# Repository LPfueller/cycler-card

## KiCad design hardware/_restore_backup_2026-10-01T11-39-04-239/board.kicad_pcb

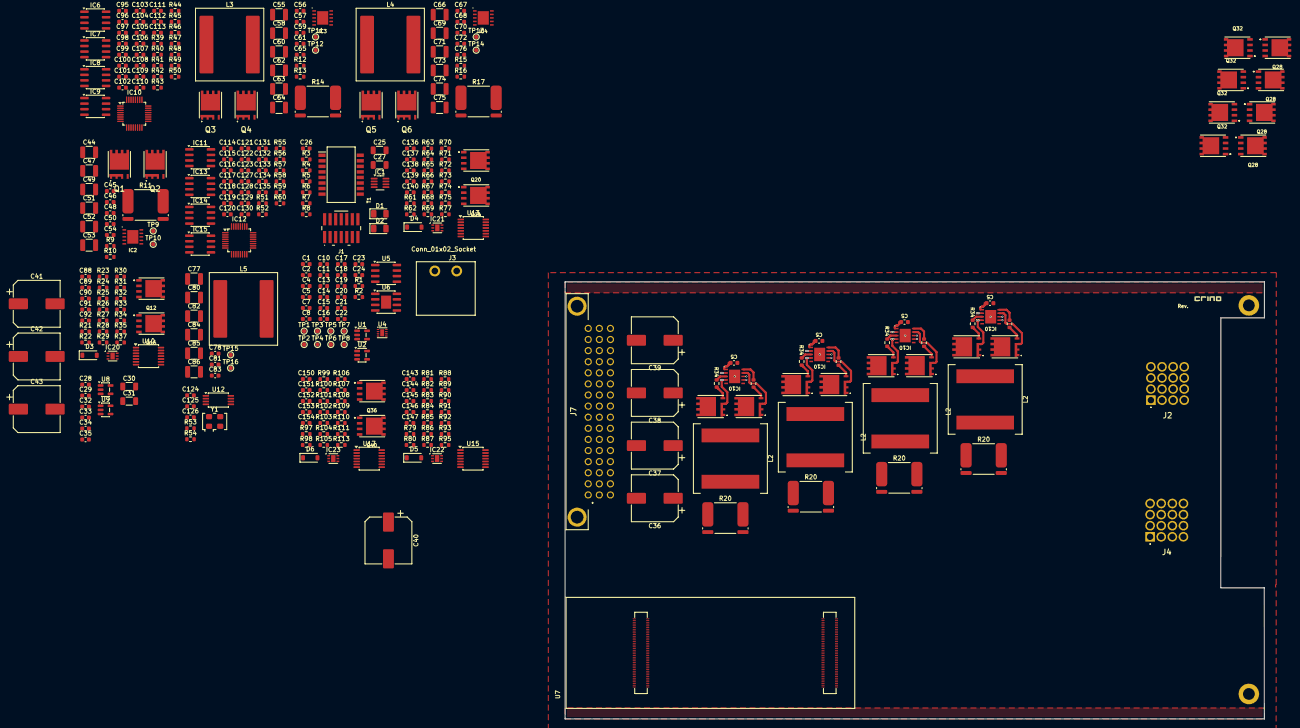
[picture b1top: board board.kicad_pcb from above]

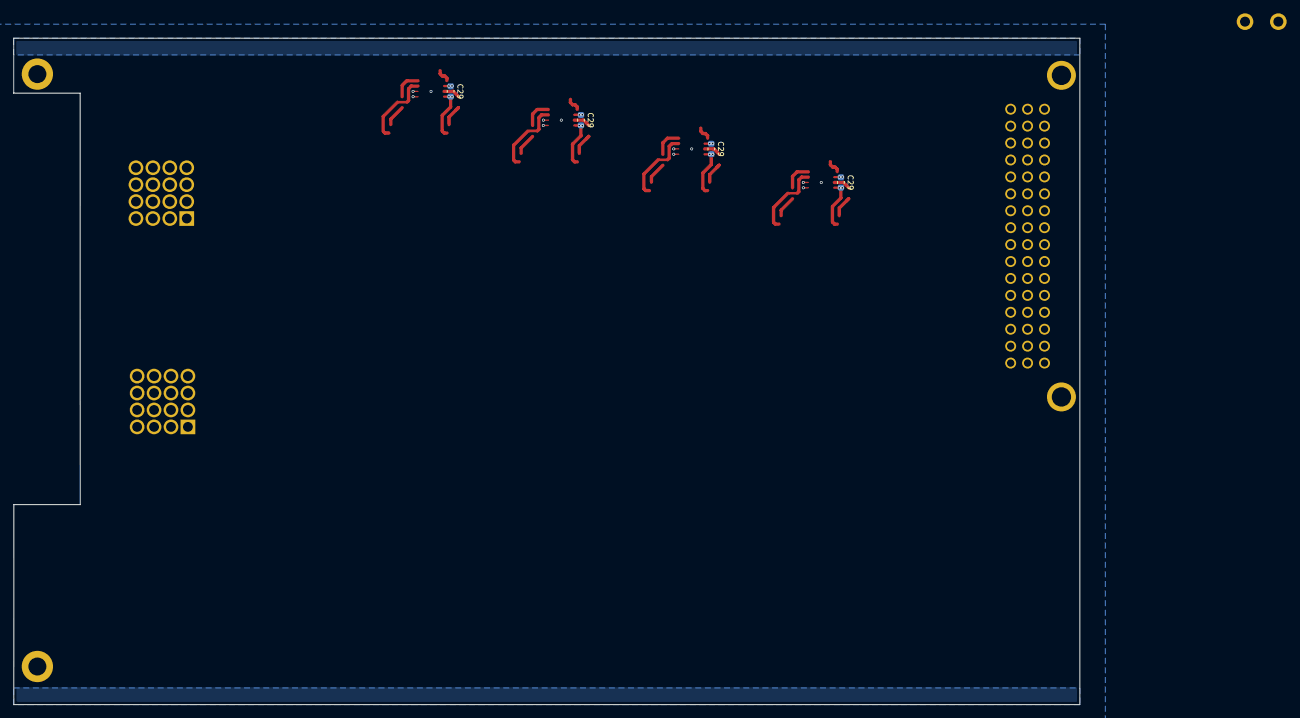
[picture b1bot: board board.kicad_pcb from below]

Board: 4 copper layers, 160.0 x 100.0 mm, 367 parts (4 on the bottom side), 222 nets.

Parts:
C1, C2, C10, C11, C15, C16, C20, C21, C23, C34, C35: 2.2u; C_0603_1608Metric
C4, C5#2, C7, C8, C17, C22, C24, C26, C29#2, C29#3, C29#4, C29#5, C32, C33, C45, C48, C50, C54, C56, C59, C61, C65, C67, C70, C72, C76, C78, C81, C83, C88, C89, C92, C95, C96, C97, C98, C99, C100, C101, C102, C108, C109, C113, C114, C115, C118, C119, C123, C124, C126, C127, C128, C130, C131, C133, C134, C136, C137, C140, C143, C144, C147, C150, C151, C154: 100n; C_0603_1608Metric
C5, C5#3, C5#4, C5#5, C14, C28, C29, C46, C57, C68, C90, C91, C107, C110, C111, C112, C117, C120, C121, C122, C125, C138, C139, C145, C146, C152, C153: 1u; C_0603_1608Metric
C13, C18: 4.7u; C_0603_1608Metric
C19: 1n; C_0603_1608Metric
C25, C27: 1n; C_1206_3216Metric
C30, C31: C; C_1206_3216Metric
C36, C37, C38, C39, C40, C41, C42, C43: 270u; CP_Elec_10x12.5
C44, C47, C49, C51, C52, C53, C55, C58, C60, C62, C63, C64, C66, C69, C71, C73, C74, C75, C77, C80, C82, C84, C85, C86: 10u; C_1210_3225Metric
C103, C104, C105, C106, C116, C129, C132, C135: 330n; C_0603_1608Metric
D1: LED_SYNC; LED_1206_3216Metric
D2: LED_ERR; LED_1206_3216Metric
D3, D4, D5, D6: 1N5817; D_SOD-123
H7, H8: MountingHole; MountingHole_2.7mm_M2.5_DIN965_Pad
H9: CrinoLogo; crino_logo
IC1: TCAN1044VDDFR; SOT-23-8_Handsoldering
IC2, IC3, IC4, IC10#2, IC10#3, IC10#4, IC10#5: UCC27212DPRR; SON80P400X400X80-11N-D
IC6, IC7, IC8, IC9, IC11, IC13, IC14, IC15: INA821ID; SOIC-8_3.9x4.9mm_P1.27mm
IC10, IC12: ADS131A04IPBS; LQFP-32_5x5mm_P0.5mm
IC20, IC21, IC22, IC23: NCV68261; DFN-6-1EP_2x2mm_P0.65mm_EP1x1.6mm
J1: Conn_ST_STDC14; FTSH-107-01-L-DV-K-TR
J2: +FORCE; 7461147
J3: Conn_01x02_Socket; Wago_231-432_001-000
J4: -FORCE; 7461147
J7: 09231482921
L2, L2#2, L2#3, L2#4, L3, L4, L5: 4.7u; L_Coilcraft_XAL1510-472
Q1, Q1#2, Q1#3, Q1#4, Q1#5, Q2, Q3, Q4, Q5, Q6, Q16, Q16#2, Q16#3, Q16#4: ISC012N04LM6; ISC012N04LM6ATMA1
Q12, Q16#5, Q20, Q24, Q28, Q28#2, Q28#3, Q28#4, Q32, Q32#2, Q32#3, Q32#4, Q36, Q40: SIRA60DP; SI7852ADPT1GE3
R1: 150k; R_0603_1608Metric
R2, R23, R63, R81, R99: 49.9k; R_0603_1608Metric
R3, R4, R5, R6: 75; R_0603_1608Metric
R7: 1.2k; R_0603_1608Metric
R8: 560; R_0603_1608Metric
R9, R10, R12, R13, R15, R15#2, R15#3, R15#4, R15#5, R16, R32, R34, R34#2, R34#3, R34#4, R34#5, R35, R72, R74, R75, R90, R92, R93, R108, R110, R111: 0; R_0603_1608Metric
R11, R14, R17, R20, R20#2, R20#3, R20#4: 1m; R_Shunt_Isabellenhuette_BVR4026
R21, R22, R61, R62, R79, R80, R97, R98: 100k; R_0603_1608Metric
R24, R64, R82, R100: 24.9k; R_0603_1608Metric
R25, R26, R65, R66, R83, R84, R101, R102: 4.99k; R_0603_1608Metric
R27, R28, R29, R30, R31, R33, R53, R54, R67, R68, R69, R70, R71, R73, R85, R86, R87, R88, R89, R91, R103, R104, R105, R106, R107, R109: 10k; R_0603_1608Metric
R37, R77, R95, R113: 10; R_0603_1608Metric
R39, R40, R41, R42: R_0603_1608Metric
R43, R44, R45, R46, R47, R48, R49, R50, R51, R52, R55, R56, R57, R58, R59, R60: 1k; R_0603_1608Metric
T1: H1102NLT; SOIC127P940X622-16N
TP1, TP2, TP3, TP4, TP5, TP6, TP7, TP8, TP9, TP10, TP11, TP12, TP13, TP14, TP15, TP16: Testpoint; TestPoint_Pad_D1.0mm
U1, U9: LP2985-5.0; SOT-23-5
U2: LP2985-10.0; SOT-23-5
U4: LM27761; Texas_DSG0008A_WSON-8-1EP_2x2mm_P0.5mm_EP0.9x1.6mm
U5: MAX6225; SOIC-8_3.9x4.9mm_P1.27mm
U6: ADP7142ARDZ-5.0; SOIC-8-1EP_3.9x4.9mm_P1.27mm_EP2.29x3mm
U7: crino-board
U8: LP2985-3.3; SOT-23-5
U10, U13, U15, U17: LM339; TSSOP-14_4.4x5mm_P0.65mm
U12: CDCV304; TSSOP-8_4.4x3mm_P0.65mm
Y1: ASFLMB-16.384MHZ-LR-T; Oscillator_SMD_EuroQuartz_XO53-4Pin_5.0x3.2mm

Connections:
/+2.5VREF: C20.2, C22.2, IC6.6 (REF), IC7.6 (REF), IC8.6 (REF), IC9.6 (REF), IC10.14 (REFEXT), IC12.14 (REFEXT), R44.1, R46.1, R48.1, R50.1, R52.1, R56.1, R58.1, R60.1, TP3.1 (1_1), U5.6 (OUT)
/+3.3V: C34.2, C107.1, C108.1, C109.1, C117.1, C118.1, C119.1, C124.1, C125.1, C126.1, IC10.15 (IOVDD_1), IC10.16 (RESV), IC10.29 (IOVDD_2), IC12.15 (IOVDD_1), IC12.16 (RESV), IC12.29 (IOVDD_2), J1.3 (VCC), R53.2, R54.2, U7.J2_23 (+3V3), U7.J2_34 (+3V3_1), U7.J2_43 (+3V3_2), U7.J2_69 (+3V3_3), U8.5 (VOUT), U12.6 (V_{DD}), Y1.4 (VDD)
/+5V: C26.1, C35.2, IC1.3 (VCC), IC1.5 (VIO), R7.1, R8.1, R31.2, R71.2, R89.2, R107.2, U9.5 (VOUT)
/+5VA: C23.2, C24.2, C111.1, C113.1, C121.1, C123.1, IC10.9 (AVDD), IC12.9 (AVDD), TP6.1 (1_1), U6.1 (VOUT), U6.2 (VOUT), U6.3 (SENSE/ADJ)
/+10VA: C1.2, C4.2, C11.2, C15.2, C16.2, C17.2, C88.1, C91.1, C92.1, C95.1, C96.1, C97.1, C98.1, C114.1, C127.1, C130.1, C133.1, C136.1, C139.1, C140.1, C143.1, C146.1, C147.1, C150.1, C153.1, C154.1, IC6.8 (+VS), IC7.8 (+VS), IC8.8 (+VS), IC9.8 (+VS), IC11.8 (+VS), IC13.8 (+VS), IC14.8 (+VS), IC15.8 (+VS), IC20.6 (IN), IC21.6 (IN), IC22.6 (IN), IC23.6 (IN), R24.1, R64.1, R82.1, R100.1, TP1.1 (1_1), U1.1 (VIN), U1.3 (ON/~OFF), U2.5 (VOUT), U5.2 (IN), U6.5 (EN), U6.7 (VIN), U6.8 (VIN), U10.3 (V+), U13.3 (V+), U15.3 (V+), U17.3 (V+)
/+12V: C30.1, J7.A9, J7.B9, J7.C9, U7.J1_21 (VIN), U7.J1_32 (VIN__1), U7.J1_41 (VIN__2), U7.J1_48 (VIN__3)
/+12VP: C5.1, C5#3.1, C5#4.1, C5#5.1, IC10#2.1 (VDD), IC10#3.1 (VDD), IC10#4.1 (VDD), IC10#5.1 (VDD)
/+12V_FIL: C2.2, C5#2.2, C28.1, C29.1, C31.1, C46.1, C57.1, C68.1, IC2.1 (VDD), IC3.1 (VDD), IC4.1 (VDD), U2.1 (VIN), U2.3 (ON/~OFF), U8.1 (VIN), U8.3 (ON/~OFF), U9.1 (VIN), U9.3 (ON/~OFF)
/+24V: C36.1, C37.1, C38.1, C39.1, J7.A1, J7.A2, J7.A3, J7.A4, J7.B1, J7.B2, J7.B3, J7.B4, J7.C1, J7.C2, J7.C3, J7.C4, Q1#2.D, Q3.D, Q5.D
/-5VA: C21.2, C89.1, C99.1, C100.1, C101.1, C102.1, C115.1, C128.1, C131.1, C134.1, C137.1, C144.1, C151.1, IC6.5 (-VS), IC7.5 (-VS), IC8.5 (-VS), IC9.5 (-VS), IC11.5 (-VS), IC13.5 (-VS), IC14.5 (-VS), IC15.5 (-VS), R1.1, R23.1, R63.1, R81.1, R99.1, TP4.1 (1_1), U4.4 (VOUT), U10.12 (V-), U13.12 (V-), U15.12 (V-), U17.12 (V-)
/ALERT1: R34.1, R35.2, U7.J1_45 (PC3)
/ALERT2: R74.1, R75.2, U7.J1_63 (PB7)
/ALERT3: R92.1, R93.2, U7.J1_62 (PA15)
/ALERT4: R110.1, R111.2, U7.J1_20 (PB0)
/GND: C1.1, C2.1, C4.1, C5.2, C5#2.1, C5#3.2, C5#4.2, C5#5.2, C7.1, C8.1, C10.1, C11.1, C13.2, C15.1, C16.1, C17.1, C18.2, C19.1, C20.1, C21.1, C22.1, C23.1, C24.1, C25.2, C26.2, C27.2, C28.2, C29.2, C30.2, C31.2, C32.1, C33.1, C34.1, C35.1, C36.2, C37.2, C38.2, C39.2, C40.2, C41.2, C42.2, C43.2, C44.2, C45.2, C46.2, C47.2, C48.2, C49.2, C50.2, C51.2, C52.2, C53.2, C55.2, C56.2, C57.2, C58.2, C59.2, C60.2, C61.2, C62.2, C63.2, C64.2, C66.2, C67.2, C68.2, C69.2, C70.2, C71.2, C72.2, C73.2, C74.2, C75.2, C77.2, C78.2, C80.2, C81.2, C82.2, C83.2, C84.2, C85.2, C86.2, C88.2, C89.2, C90.2, C91.2, C92.2, C95.2, C96.2, C97.2, C98.2, C99.2, C100.2, C101.2, C102.2, C107.2, C108.2, C109.2, C111.2, C112.2, C113.2, C114.2, C115.2, C117.2, C118.2, C119.2, C121.2, C122.2, C123.2, C124.2, C125.2, C126.2, C127.2, C128.2, C130.2, C131.2, C133.2, C134.2, C136.2, C137.2, C138.2, C139.2, C140.2, C143.2, C144.2, C145.2, C146.2, C147.2, C150.2, C151.2, C152.2, C153.2, C154.2, IC1.2 (GND), IC1.8 (STB), IC2.9 (VSS), IC2.11 (EP), IC3.9 (VSS), IC3.11 (EP), IC4.9 (VSS), IC4.11 (EP), IC10.10 (AVSS), IC10.11 (VNCP), IC10.27 (GND), IC10.31 (M1), IC10.32 (M2), IC10#2.9 (VSS), IC10#2.11 (EP), IC10#3.9 (VSS), IC10#3.11 (EP), IC10#4.9 (VSS), IC10#4.11 (EP), IC10#5.9 (VSS), IC10#5.11 (EP), IC11.6 (REF), IC12.10 (AVSS), IC12.11 (VNCP), IC12.27 (GND), IC12.31 (M1), IC12.32 (M2), IC13.6 (REF), IC14.6 (REF), IC15.6 (REF), IC20.3 (D), IC20.5 (GND), IC20.7 (EP), IC21.3 (D), IC21.5 (GND), IC21.7 (EP), IC22.3 (D), IC22.5 (GND), IC22.7 (EP), IC23.3 (D), IC23.5 (GND), IC23.7 (EP), J1.5 (GND), J1.7 (GND), J1.11 (GNDDetect), J4.1 (Pin_1_1), J7.A5, J7.A6, J7.A7, J7.A8, J7.A10, J7.A11, J7.A12, J7.A13, J7.A14, J7.B5, J7.B6, J7.B7, J7.B8, J7.B10, J7.B13, J7.B14, J7.B15, J7.B16, J7.C5, J7.C6, J7.C7, J7.C8, J7.C10, J7.C13, J7.C14, J7.C15, J7.C16, Q2.S, Q4.S, Q6.S, Q16.S, Q16#2.S, Q16#3.S, Q16#4.S, R2.2, R22.1, R25.2, R26.2, R32.1, R35.1, R62.1, R65.2, R66.2, R72.1, R75.1, R80.1, R83.2, R84.2, R90.1, R93.1, R98.1, R101.2, R102.2, R108.1, R111.1, TP2.1 (1_1), TP5.1 (1_1), TP7.1 (1_1), TP8.1 (1_1), U1.2 (GND), U2.2 (GND), U4.2 (GND), U4.9 (PAD), U5.4 (GND), U6.4 (GND), U6.9 (GND), U7.J1_22 (GND), U7.J1_31 (GND__1), U7.J1_42 (GND__2), U7.J1_47 (GND__3), U7.J1_54 (GND__4), U7.J2_24 (GND_1), U7.J2_33 (GND_1__1), U7.J2_44 (GND_1__2), U7.J2_57 (GND_1__3), U7.J2_70 (GND_1__4), U8.2 (GND), U9.2 (GND), U12.4 (GND), Y1.2 (GND)
/PWM1_H: IC2.7 (HI), U7.J1_38 (PC6)
/PWM1_L: IC2.8 (LI), U7.J1_40 (PC7)
/PWM2_H: IC3.7 (HI), U7.J1_44 (PC8)
/PWM2_L: IC3.8 (LI), U7.J1_46 (PC9)
/PWM3_H: IC4.7 (HI), U7.J1_50 (PA8)
/PWM3_L: IC4.8 (LI), U7.J1_52 (PA9)
/PWMH1: IC10#2.7 (HI), IC10#3.7 (HI), IC10#4.7 (HI), IC10#5.7 (HI)
/PWML1: IC10#2.8 (LI), IC10#3.8 (LI), IC10#4.8 (LI), IC10#5.8 (LI)
/PWR_ENABLE1: U7.J1_43 (PA0), U10.11 (+)
/PWR_ENABLE2: U7.J1_61 (PB9), U13.11 (+)
/PWR_ENABLE3: U7.J1_64 (PC12), U15.11 (+)
/PWR_ENABLE4: U7.J1_18 (PB1), U17.11 (+)
/RXB_N: J7.C11, T1.16 (TX+)
/RXB_P: J7.C12, T1.14 (TX-)
/TXB_N: J7.B11, T1.11 (RX+)
/TXB_P: J7.B12, T1.9 (RX-)
/V_SENSE1: IC11.7 (OUT), R21.2, R51.1
/V_SENSE1_N: IC11.1 (-IN), J3.2
/V_SENSE1_P: IC11.4 (+IN), J3.1
/V_SENSE2: IC13.7 (OUT), R55.1, R61.2
/V_SENSE3: IC14.7 (OUT), R57.1, R79.2
/V_SENSE4: IC15.7 (OUT), R59.1, R97.2
/V_SHUNT1_N: IC6.1 (-IN), R11.3
/V_SHUNT1_P: IC6.4 (+IN), R11.2
/V_SHUNT2_N: IC7.1 (-IN), R14.3
/V_SHUNT2_P: IC7.4 (+IN), R14.2
/V_SHUNT3_N: IC8.1 (-IN), R17.3
/V_SHUNT3_P: IC8.4 (+IN), R17.2
/V_SHUNT4_N: IC9.1 (-IN), R20.3, R20#2.3, R20#3.3, R20#4.3
/V_SHUNT4_P: IC9.4 (+IN), R20.2, R20#2.2, R20#3.2, R20#4.2
/adc/1.MISO: IC10.21 (DOUT), U7.J1_69 (WTD_(PB4))
/adc/1.MOSI: IC10.20 (DIN), U7.J1_67 (PB5)
/adc/1.SCK: IC10.22 (SCLK), U7.J1_29 (PA5)
/adc/2.MISO: IC12.21 (DOUT), U7.J1_34 (PB14)
/adc/2.MOSI: IC12.20 (DIN), U7.J1_36 (PB15)
/adc/2.SCK: IC12.22 (SCLK), U7.J1_30 (PB13)
/adc/ADC_CLK1: IC10.25 (XTAL1/CLKIN), U12.3 (1Y0)
/adc/ADC_CLK2: IC12.25 (XTAL1/CLKIN), U12.5 (1Y1)
/adc/ADS131A02.ADC_CS: IC12.23 (~CS), U7.J1_53 (PC0)
/adc/ADS131A02.ADC_NDRDY: IC12.19 (~DRDY), U7.J1_51 (PC1)
/adc/ADS131A02.ADC_NRST: IC12.17 (~RESET), U7.J1_49 (PC2)
/adc/ADS131A04.ADC_CS: IC10.23 (~CS), U7.J1_59 (PC13)
/adc/ADS131A04.ADC_NDRDY: IC10.19 (~DRDY), U7.J1_57 (PC14)
/adc/ADS131A04.ADC_NRST: IC10.17 (~RESET), U7.J1_55 (PC15)
/adc/adc_current_block/V_SHUNT_BUFFERED1_N: C103.2, IC10.1 (AIN1N), R44.2
/adc/adc_current_block/V_SHUNT_BUFFERED1_P: C103.1, IC10.2 (AIN1P), R43.2
/adc/adc_current_block/V_SHUNT_BUFFERED2_N: C104.2, IC10.3 (AIN2N), R46.2
/adc/adc_current_block/V_SHUNT_BUFFERED2_P: C104.1, IC10.4 (AIN2P), R45.2
/adc/adc_current_block/V_SHUNT_BUFFERED3_N: C105.2, IC10.5 (AIN3N), R48.2
/adc/adc_current_block/V_SHUNT_BUFFERED3_P: C105.1, IC10.6 (AIN3P), R47.2
/adc/adc_current_block/V_SHUNT_BUFFERED4_N: C106.2, IC10.7 (AIN4N), R50.2
/adc/adc_current_block/V_SHUNT_BUFFERED4_P: C106.1, IC10.8 (AIN4P), R49.2
/adc/adc_voltage_block/V_SENSE_BUFFERED1_N: C116.2, IC12.1 (AIN1N), R52.2
/adc/adc_voltage_block/V_SENSE_BUFFERED1_P: C116.1, IC12.2 (AIN1P), R51.2
/adc/adc_voltage_block/V_SENSE_BUFFERED2_N: C129.2, IC12.3 (AIN2N), R56.2
/adc/adc_voltage_block/V_SENSE_BUFFERED2_P: C129.1, IC12.4 (AIN2P), R55.2
/adc/adc_voltage_block/V_SENSE_BUFFERED3_N: C132.2, IC12.5 (AIN3N), R58.2
/adc/adc_voltage_block/V_SENSE_BUFFERED3_P: C132.1, IC12.6 (AIN3P), R57.2
/adc/adc_voltage_block/V_SENSE_BUFFERED4_N: C135.2, IC12.7 (AIN4N), R60.2
/adc/adc_voltage_block/V_SENSE_BUFFERED4_P: C135.1, IC12.8 (AIN4P), R59.2
/backplane_connector/1.CANH: IC1.7 (CANH), J7.A15
/backplane_connector/1.CANL: IC1.6 (CANL), J7.A16
/battery_connector/+FORCE: C40.1, C41.1, C42.1, C43.1, J2.1 (Pin_1_1), Q16#5.D, Q24.D, Q32.D, Q32#2.D, Q32#3.D, Q32#4.D, Q40.D
/battery_switch/+OUTP: R20#3.4, R20#4.4
/battery_switch/OUT3_P: Q28.D, Q28#2.D, Q28#3.D, Q28#4.D
/battery_switch/V_DAC_MAX: U7.J1_33 (PA4), U10.7 (+), U13.7 (+), U15.7 (+), U17.7 (+)
/battery_switch/V_DAC_MIN: U7.J1_27 (PA6), U10.8 (-), U13.8 (-), U15.8 (-), U17.8 (-)
/battery_switch/battery_switch_block1/V_SENSE_DIV: R21.1, R22.2, U10.5 (+), U10.6 (-), U10.9 (+)
/battery_switch/battery_switch_block2/V_SENSE_DIV: R61.1, R62.2, U13.5 (+), U13.6 (-), U13.9 (+)
/battery_switch/battery_switch_block3/V_SENSE_DIV: R79.1, R80.2, U15.5 (+), U15.6 (-), U15.9 (+)
/battery_switch/battery_switch_block4/V_SENSE_DIV: R97.1, R98.2, U17.5 (+), U17.6 (-), U17.9 (+)
/crino-board/CAN1_RX: IC1.4 (RXD), U7.J1_28 (PB12)
/crino-board/CAN1_TX: IC1.1 (TXD), U7.J1_65 (PB6)
/crino-board/LED_ERR: D2.1 (K), U7.J1_23 (PC5)
/crino-board/LED_SYNC: D1.1 (K), U7.J1_25 (PC4)
/crino-board/NRST: J1.12 (~RST), U7.J1_73 (~RST_STM)
/crino-board/RX_N: T1.1 (TD+), U7.J1_7 (ETHERNET_RD-)
/crino-board/RX_P: T1.3 (TD-), U7.J1_5 (ETHERNET_RD+)
/crino-board/SWCLK: J1.6 (JCLK/SWCLK), U7.J1_77 (SWCLK_(PA14))
/crino-board/SWDIO: J1.4 (JTMS/SWDIO), U7.J1_75 (SWDIO_(PA13))
/crino-board/SWO: J1.8 (JTDO/SWO), U7.J1_79 (SWO_(PB3))
/crino-board/TX_N: T1.6 (RD+), U7.J1_3 (ETHERNET_TD-)
/crino-board/TX_P: T1.8 (RD-), U7.J1_1 (ETHERNET_TD+)
/power_stage/dcdc_block_1/HB: C54.1, IC2.2 (HB)
/power_stage/dcdc_block_1/HO: Q1#2.G, R9.1
/power_stage/dcdc_block_1/HS: C54.2, IC2.4 (HS), L2.1, L2#2.1, L2#3.1, L2#4.1, Q1#2.S, Q2.D
/power_stage/dcdc_block_1/LO: Q2.G, R10.2
/power_stage/dcdc_block_1/VIN_IND: C44.1, C45.1, C47.1, C48.1, C49.1, C50.1, C51.1, C52.1, C53.1
/power_stage/dcdc_block_2/HB: C65.1, IC3.2 (HB)
/power_stage/dcdc_block_2/HO: Q3.G, R12.1
/power_stage/dcdc_block_2/HS: C65.2, IC3.4 (HS), L3.1, Q3.S, Q4.D
/power_stage/dcdc_block_2/LO: Q4.G, R13.2
/power_stage/dcdc_block_2/VIN_IND: C55.1, C56.1, C58.1, C59.1, C60.1, C61.1, C62.1, C63.1, C64.1
/power_stage/dcdc_block_3/HB: C76.1, IC4.2 (HB)
/power_stage/dcdc_block_3/HO: Q5.G, R15#2.1
/power_stage/dcdc_block_3/HS: C76.2, IC4.4 (HS), L4.1, Q5.S, Q6.D
/power_stage/dcdc_block_3/LO: Q6.G, R16.2
/power_stage/dcdc_block_3/VIN_IND: C66.1, C67.1, C69.1, C70.1, C71.1, C72.1, C73.1, C74.1, C75.1
/power_stage/dcdc_block_4/VIN_IND: C77.1, C78.1, C80.1, C81.1, C82.1, C83.1, C84.1, C85.1, C86.1
/power_stage_1/HB: C29#2.1, C29#3.1, C29#4.1, C29#5.1, IC10#2.2 (HB), IC10#3.2 (HB), IC10#4.2 (HB), IC10#5.2 (HB)
/power_stage_1/HO: Q1.G, Q1#3.G, Q1#4.G, Q1#5.G, R34#2.1, R34#3.1, R34#4.1, R34#5.1
/power_stage_1/HS: C29#2.2, C29#3.2, C29#4.2, C29#5.2, IC10#2.4 (HS), IC10#3.4 (HS), IC10#4.4 (HS), IC10#5.4 (HS), Q1.S, Q1#3.S, Q1#4.S, Q1#5.S, Q16.D, Q16#2.D, Q16#3.D, Q16#4.D
/power_stage_1/LO: Q16.G, Q16#2.G, Q16#3.G, Q16#4.G, R15.2, R15#3.2, R15#4.2, R15#5.2
/power_stage_1/VIN_IND: Q1.D, Q1#3.D, Q1#4.D, Q1#5.D
unnamed: C25.1, R3.2, R4.2
unnamed: C27.1, R5.2, R6.2
unnamed: D1.2 (A), R7.2
unnamed: D2.2 (A), R8.2
unnamed: D3.2 (A), R32.2
unnamed: D3.1 (K), R27.2, R28.2, R29.2, R30.2, R31.1, R33.2
unnamed: D4.2 (A), R72.2
unnamed: D4.1 (K), R67.2, R68.2, R69.2, R70.2, R71.1, R73.2
unnamed: D5.2 (A), R90.2
unnamed: D5.1 (K), R85.2, R86.2, R87.2, R88.2, R89.1, R91.2
unnamed: D6.2 (A), R108.2
unnamed: D6.1 (K), R103.2, R104.2, R105.2, R106.2, R107.1, R109.2
unnamed: R11.4, TP10.1 (1_1)
unnamed: R14.4, TP12.1 (1_1)
unnamed: R17.4, TP14.1 (1_1)
unnamed: R20.4, R20#2.4, TP16.1 (1_1)
unnamed: IC2.3 (HO), R9.2
unnamed: IC2.10 (LO), R10.1
unnamed: IC3.3 (HO), R12.2
unnamed: IC3.10 (LO), R13.1
unnamed: IC4.3 (HO), R15#2.2
unnamed: IC4.10 (LO), R16.1
unnamed: IC6.7 (OUT), R43.1
unnamed: IC6.2 (RG_1), R39.1
unnamed: IC6.3 (RG_2), R39.2
unnamed: IC7.7 (OUT), R45.1
unnamed: IC7.2 (RG_1), R40.1
unnamed: IC7.3 (RG_2), R40.2
unnamed: IC8.7 (OUT), R47.1
unnamed: IC8.2 (RG_1), R41.1
unnamed: IC8.3 (RG_2), R41.2
unnamed: IC9.7 (OUT), R49.1
unnamed: IC9.2 (RG_1), R42.1
unnamed: IC9.3 (RG_2), R42.2
unnamed: C112.1, IC10.28 (CAP)
unnamed: IC10#2.3 (HO), IC10#3.3 (HO), IC10#4.3 (HO), IC10#5.3 (HO), R34#2.2, R34#3.2, R34#4.2, R34#5.2
unnamed: IC10#2.10 (LO), IC10#3.10 (LO), IC10#4.10 (LO), IC10#5.10 (LO), R15.1, R15#3.1, R15#4.1, R15#5.1
unnamed: C110.2, IC10.13 (REFN)
unnamed: C110.1, IC10.12 (REFP)
unnamed: C122.1, IC12.28 (CAP)
unnamed: C120.2, IC12.13 (REFN)
unnamed: C120.1, IC12.12 (REFP)
unnamed: C90.1, IC20.4 (EN), R33.1, R34.2
unnamed: IC20.2 (G), R37.1
unnamed: IC20.1 (S), Q12.S, Q16#5.S
unnamed: C138.1, IC21.4 (EN), R73.1, R74.2
unnamed: IC21.2 (G), R77.1
unnamed: IC21.1 (S), Q20.S, Q24.S
unnamed: C145.1, IC22.4 (EN), R91.1, R92.2
unnamed: IC22.2 (G), R95.1
unnamed: IC22.1 (S), Q28.S, Q28#2.S, Q28#3.S, Q28#4.S, Q32.S, Q32#2.S, Q32#3.S, Q32#4.S
unnamed: C152.1, IC23.4 (EN), R109.1, R110.2
unnamed: IC23.2 (G), R113.1
unnamed: IC23.1 (S), Q36.S, Q40.S
unnamed: L2.2, L2#2.2, L2#3.2, L2#4.2, R11.1, TP9.1 (1_1)
unnamed: L3.2, R14.1, TP11.1 (1_1)
unnamed: L4.2, R17.1, TP13.1 (1_1)
unnamed: L5.2, R20.1, R20#2.1, R20#3.1, R20#4.1, TP15.1 (1_1)
unnamed: Q12.G, Q16#5.G, R37.2
unnamed: Q20.G, Q24.G, R77.2
unnamed: Q28.G, Q28#2.G, Q28#3.G, Q28#4.G, Q32.G, Q32#2.G, Q32#3.G, Q32#4.G, R95.2
unnamed: Q36.G, Q40.G, R113.2
unnamed: R27.1, U10.2
unnamed: R28.1, U10.13
unnamed: R29.1, U10.1
unnamed: R30.1, U10.14
unnamed: R67.1, U13.2
unnamed: R68.1, U13.13
unnamed: R69.1, U13.1
unnamed: R70.1, U13.14
unnamed: R85.1, U15.2
unnamed: R86.1, U15.13
unnamed: R87.1, U15.1
unnamed: R88.1, U15.14
unnamed: R103.1, U17.2
unnamed: R104.1, U17.13
unnamed: R105.1, U17.1
unnamed: R106.1, U17.14
unnamed: R5.1, T1.2 (CT_1)
unnamed: R6.1, T1.7 (CT_2)
unnamed: R4.1, T1.10 (CT_3)
unnamed: R3.1, T1.15 (CT_4)
unnamed: C7.2, U1.4 (BP)
unnamed: C10.2, C13.1, U1.5 (VOUT), U4.1 (VIN), U4.6 (EN)
unnamed: C8.2, U2.4 (BP)
unnamed: C14.1, U4.8 (C+)
unnamed: C14.2, U4.7 (C-)
unnamed: C18.1, U4.3 (CPOUT)
unnamed: R1.2, R2.1, U4.5 (VFB)
unnamed: C19.2, U6.6 (SS)
unnamed: C32.2, U8.4 (BP)
unnamed: C33.2, U9.4 (BP)
unnamed: R23.2, R25.1, U10.4 (-)
unnamed: R24.2, R26.1, U10.10 (-)
unnamed: U12.1 (CLKIN), Y1.3 (OUTPUT)
unnamed: R54.1, U12.2 (OE)
unnamed: R63.2, R65.1, U13.4 (-)
unnamed: R64.2, R66.1, U13.10 (-)
unnamed: R81.2, R83.1, U15.4 (-)
unnamed: R82.2, R84.1, U15.10 (-)
unnamed: R99.2, R101.1, U17.4 (-)
unnamed: R100.2, R102.1, U17.10 (-)
unnamed: R53.1, Y1.1 (STANDBY)

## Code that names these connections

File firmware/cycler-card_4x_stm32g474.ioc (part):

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Mcu.Name=STM32G474R(B-C-E)Tx
Mcu.Package=LQFP64
Mcu.UserName=STM32G474RETx
PA0.GPIOParameters=GPIO_Label
PA0.GPIO_Label=PWR_ENABLE
PA0.Signal=GPIO_Output
PA10.Mode=Output_TB1TB2
PA10.Signal=HRTIM1_CHB1
PA11.Mode=Output_TB1TB2
PA11.Signal=HRTIM1_CHB2
PA13.Mode=Trace_Asynchronous_SW
PA13.Signal=SYS_JTMS-SWDIO
PA14.Mode=Trace_Asynchronous_SW
PA14.Signal=SYS_JTCK-SWCLK
PA4.Signal=COMP_DAC11_group
PA5.Mode=Full_Duplex_Master
PA5.Signal=SPI1_SCK
PA6.Signal=COMP_DAC21_group
PA8.Mode=Output_TA1TA2
PA8.Signal=HRTIM1_CHA1
PA9.Mode=Output_TA1TA2
PA9.Signal=HRTIM1_CHA2
PB13.Mode=Full_Duplex_Master
PB13.Signal=SPI2_SCK
PB14.Mode=Full_Duplex_Master
PB14.Signal=SPI2_MISO
PB15.Mode=Full_Duplex_Master
PB15.Signal=SPI2_MOSI
PB3.Mode=Trace_Asynchronous_SW
PB3.Signal=SYS_JTDO-SWO
PB4.Mode=Full_Duplex_Master
PB4.Signal=SPI1_MISO
PB5.Mode=Full_Duplex_Master
PB5.Signal=SPI1_MOSI
PC0.GPIOParameters=GPIO_Label
PC0.GPIO_Label=ADS131A02.ADC_CS
PC0.Signal=GPIO_Output
PC1.GPIOParameters=GPIO_Label
PC1.GPIO_Label=ADS131A02.ADC_NDRDY
PC1.Signal=GPIO_Input
PC13.GPIOParameters=GPIO_Label
PC13.GPIO_Label=ADS131A04.ADC_CS
PC13.Signal=GPIO_Output
PC14-OSC32_IN.GPIOParameters=GPIO_Label
PC14-OSC32_IN.GPIO_Label=ADS131A04.ADC_NDRDY
PC14-OSC32_IN.Signal=GPIO_Input
PC15-OSC32_OUT.GPIOParameters=GPIO_Label
PC15-OSC32_OUT.GPIO_Label=ADS131A04.ADC_NRST
PC15-OSC32_OUT.Signal=GPIO_Output
PC2.GPIOParameters=GPIO_Label
PC2.GPIO_Label=ADS131A02.ADC_NRST
PC2.Signal=GPIO_Output
PC3.GPIOParameters=GPIO_Label
PC3.GPIO_Label=ALERT
PC3.Signal=GPIO_Input
PC4.GPIOParameters=GPIO_Label
PC4.GPIO_Label=LED_SYNC
PC4.Signal=GPIO_Output
PC5.GPIOParameters=GPIO_Label
PC5.GPIO_Label=LED_ERR
PC5.Signal=GPIO_Output
PC6.Mode=Output_TF1TF2
PC6.Signal=HRTIM1_CHF1
PC7.Mode=Output_TF1TF2
PC7.Signal=HRTIM1_CHF2
PC8.Mode=Output_TE1TE2
PC8.Signal=HRTIM1_CHE1
PC9.Mode=Output_TE1TE2
PC9.Signal=HRTIM1_CHE2
RCC.HSE_VALUE=8000000
RCC.SYSCLKFreq_VALUE=16000000
board=custom

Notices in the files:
parts and their libraries:
Copyright 2016 Accelerated Designs. All rights reserved.
